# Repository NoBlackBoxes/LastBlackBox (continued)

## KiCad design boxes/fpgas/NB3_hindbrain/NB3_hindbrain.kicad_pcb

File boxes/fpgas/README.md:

# The Last Black Box : FPGAs
In this box, you will learn about fpgas...

## FPGAs
Field-programmable-gate-arrays-are-awesome.

<details><summary><i>Materials</i></summary><p>

Name|Depth|Description| # |Package|Data|Link|
:-------|:---:|:----------|:-----:|:-:|:--:|:--:|
NB3 Hindbrain|10|ICE40UP5K dev board with ADC/DAC|1|Circuit Boards|[-D-](/boxes/fpgas/NB3_hindbrain)|[-L-](VK)
Cable (MicroUSB-1m)|10|Micro-USB to Type-A cable (1 m)|1|Cables (001)|[-D-](/boxes/fpgas/)|[-L-](https://www.amazon.co.uk/gp/product/B07GBCKX49)

</p></details><hr>

### Hardware Description Languages
> Describing hardware layouts is very different than describing software algorithms. Hardware description languages allow you to describe precisely what pieces of transistor logic you want. They come in many flavours, but the most popular are **Verilog** and **VHDL**.

# Project

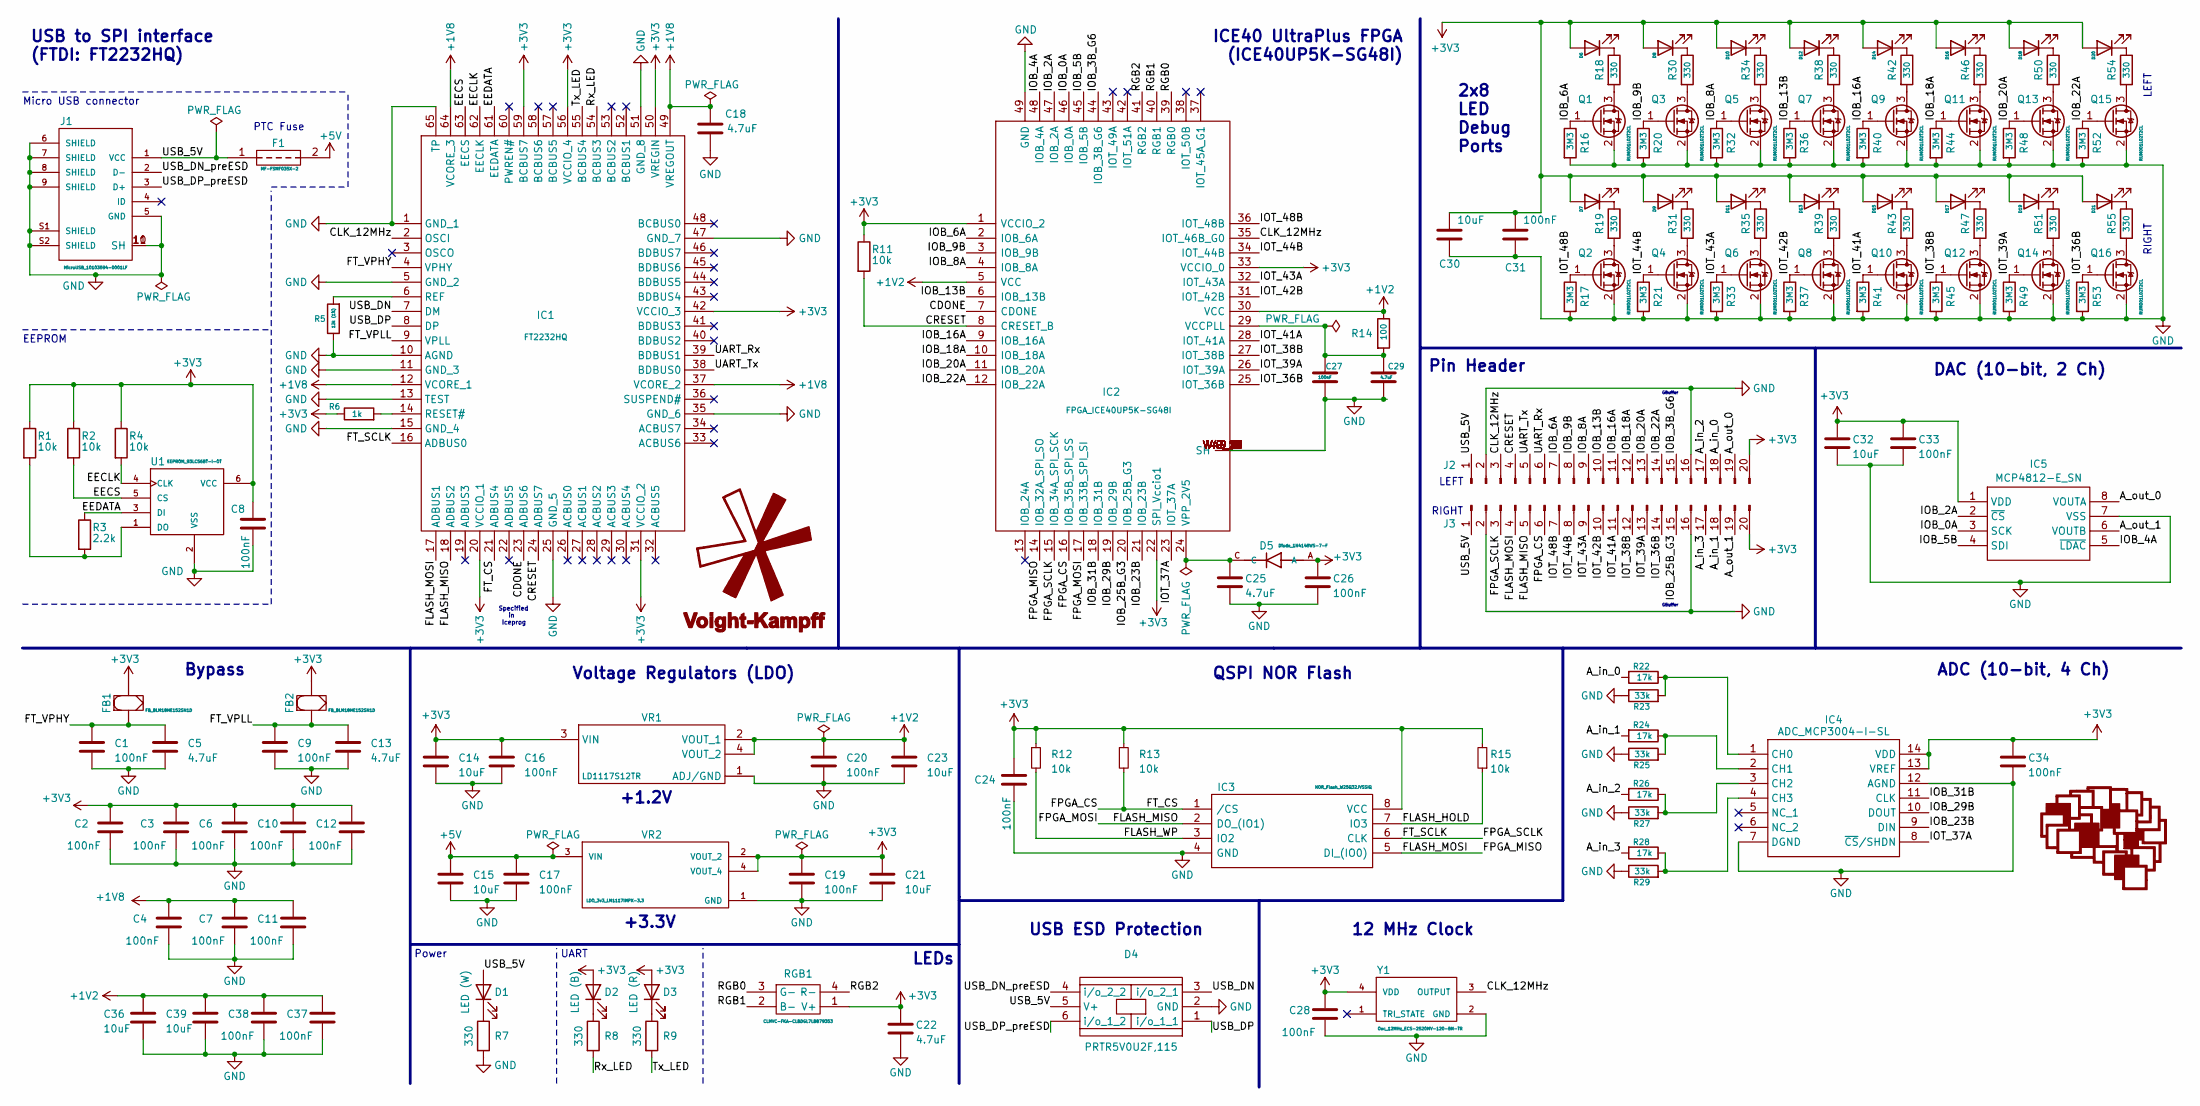
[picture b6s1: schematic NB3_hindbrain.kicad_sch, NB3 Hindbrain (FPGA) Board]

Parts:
C1, C2, C3, C4, C6, C7, C8, C9, C10, C11, C12, C16, C17, C19, C20, C24, C26, C27, C28, C31, C33, C34, C37, C38: 100nF; C_0402_1005Metric
C5, C13, C18, C22, C25, C29: 4.7uF; C_0603_1608Metric
C14, C15, C21, C23, C30, C32, C36, C39: 10uF; C_0603_1608Metric
D1: LED (W); LED_0402_1005Metric
D2, D6, D8, D10, D12, D14, D16, D18, D20: LED (B); LED_0402_1005Metric
D3, D7, D9, D11, D13, D15, D17, D19, D21: LED (R); LED_0402_1005Metric
D4: PRTR5V0U2F,115; ESD_Diodes_PRTR5V0U2F-115; Mouser Part Number 771-PRTR5V0U2F-T/R
D5: Diode_1N4148WS-7-F
F1: MF-FSMF035X-2; PTC_MF-FSMF035X-2; Mouser Part Number 652-MFFSMF035X-2
FB1, FB2: FB_BLM18HE152SN1D
G1: LOGO; Logo_NBB_5mm
G2: Logo_VK; Logo_VK_5mm
IC1: FT2232HQ; USBtoSerial_FT2232HQ; Mouser Part Number 895-FT2232HQ
IC2: FPGA_ICE40UP5K-SG48I; Manufacturer_Part_Number ICE40UP5K-SG48I; Mouser Part Number 842-ICE40UP5K-SG48I
IC3: NOR_Flash_W25Q32JVSSIQ; Manufacturer_Part_Number W25Q32JVSSIQ; Mouser Part Number 454-W25Q32JVSSIQ
IC4: ADC_MCP3004-I-SL; Mouser Part Number 579-MCP3004-I/SL
IC5: MCP4812-E_SN; DAC_MCP4812-E-SN; Mouser Part Number 579-MCP4812-E/SN
J1: MicroUSB_10103594-0001LF
J2, J3: Conn_01x20_Pin; PinHeader_1x20_P2.54mm_Vertical
Q1, Q2, Q3, Q4, Q5, Q6, Q7, Q8, Q9, Q10, Q11, Q12, Q13, Q14, Q15, Q16: RUM001L02T2CL; MOSFET_Nch_SOT-723_RUM001L02T2CL
R1, R2, R4, R11, R12, R13, R15: 10k; R_0402_1005Metric
R3: 2.2k; R_0402_1005Metric
R5: 12k (1%); R_0402_1005Metric
R6: 1k; R_0402_1005Metric
R7, R8, R9, R18, R19, R30, R31, R34, R35, R38, R39, R42, R43, R46, R47, R50, R51, R54, R55: 330; R_0402_1005Metric
R14: 100; R_0402_1005Metric
R16, R17, R20, R21, R32, R33, R36, R37, R40, R41, R44, R45, R48, R49, R52, R53: 3M3; R_0402_1005Metric
R22, R24, R26, R28: 17k; R_0402_1005Metric
R23, R25, R27, R29: 33k; R_0402_1005Metric
RGB1: CLMVC-FKA-CLBDGL7LBB79353; RGB_CLMVC-FKA-CLBDGL7LBB79353; Mouser Part Number 941-CLMVCFKACLBDGL7L
U1: EEPROM_93LC56BT-I-OT
VR1: LD1117S12TR; LDO_1v2_LD1117S12TR; Mouser Part Number 511-LD1117S12
VR2: LDO_3v3_LM1117IMPX-3.3; PARTREV O
Y1: Osc_12MHz_ECS-2520MV-120-BN-TR

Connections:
+1V2: C20.1, C23.1, C36.1, C37.2, C38.2, C39.1, IC2.5 (VCC), IC2.30 (VCC), R14.1, VR1.2 (VOUT_1), VR1.4 (VOUT_2)
+1V8: C4.2, C7.2, C11.2, C18.1, IC1.12 (VCORE_1), IC1.37 (VCORE_2), IC1.49 (VREGOUT), IC1.64 (VCORE_3)
+3V3: C2.2, C3.2, C6.2, C8.1, C10.2, C12.2, C14.1, C16.1, C19.1, C21.1, C22.1, C24.2, C26.1, C28.2, C30.1, C31.1, C32.1, C33.1, C34.1, D2.2 (A), D3.2 (A), D5.A, D6.2 (A), D7.2 (A), D8.2 (A), D9.2 (A), D10.2 (A), D11.2 (A), D12.2 (A), D13.2 (A), D14.2 (A), D15.2 (A), D16.2 (A), D17.2 (A), D18.2 (A), D19.2 (A), D20.2 (A), D21.2 (A), FB1.2, FB2.2, IC1.20 (VCCIO_1), IC1.31 (VCCIO_2), IC1.42 (VCCIO_3), IC1.50 (VREGIN), IC1.56 (VCCIO_4), IC1.59 (BCBUS7), IC2.1 (VCCIO_2), IC2.22 (SPI_Vccio1), IC2.33 (VCCIO_0), IC3.8 (VCC), IC4.13 (VREF), IC4.14 (VDD), IC5.1 (VDD), J2.20, J3.20, R1.1, R2.1, R4.1, R6.1, R11.1, R12.1, R13.1, R15.2, RGB1.1 (V+), U1.6 (VCC), VR1.3 (VIN), VR2.2 (VOUT_2), VR2.4 (VOUT_4), Y1.4 (VDD)
+5V: C15.1, C17.1, F1.2, VR2.3 (VIN)
/A_in_0: J2.18, R22.2
/A_in_1: J3.18, R24.2
/A_in_2: J2.17, R26.2
/A_in_3: J3.17, R28.2
/A_out_0: IC5.8 (VOUTA), J2.19
/A_out_1: IC5.6 (VOUTB), J3.19
/CDONE: IC1.23 (ADBUS6), IC2.7 (CDONE)
/CLK_12MHz: IC1.2 (OSCI), IC2.35 (IOT_46B_G0), J2.3, Y1.3 (OUTPUT)
/CRESET: IC1.24 (ADBUS7), IC2.8 (CRESET_B), J2.4, R11.2
/EECLK: IC1.62 (EECLK), R4.2, U1.4 (CLK)
/EECS: IC1.63 (EECS), R2.2, U1.5 (CS)
/EEDATA: IC1.61 (EEDATA), R3.1, U1.3 (DI)
/FLASH_HOLD: IC3.7 (IO3), R15.1
/FLASH_MISO: IC1.18 (ADBUS2), IC2.17 (IOB_33B_SPI_SI), IC3.2 (DO_(IO1)), J3.5
/FLASH_MOSI: IC1.17 (ADBUS1), IC2.14 (IOB_32A_SPI_SO), IC3.5 (DI_(IO0)), J3.4
/FLASH_WP: IC3.3 (IO2), R12.2
/FPGA_CS: IC1.21 (ADBUS4), IC2.16 (IOB_35B_SPI_SS), IC3.1 (/CS), J3.6, R13.2
/FPGA_SCLK: IC1.16 (ADBUS0), IC2.15 (IOB_34A_SPI_SCK), IC3.6 (CLK), J3.3
/FT_VPHY: C1.1, C5.1, FB1.1, IC1.4 (VPHY)
/FT_VPLL: C9.1, C13.1, FB2.1, IC1.9 (VPLL)
/IOB_0A: IC2.46 (IOB_0A), IC5.3 (SCK)
/IOB_2A: IC2.47 (IOB_2A), IC5.2 (~CS)
/IOB_3B_G6: IC2.44 (IOB_3B_G6), J2.15
/IOB_4A: IC2.48 (IOB_4A), IC5.5 (~LDAC)
/IOB_5B: IC2.45 (IOB_5B), IC5.4 (SDI)
/IOB_6A: IC2.2 (IOB_6A), J2.7, Q1.1 (G), R16.1
/IOB_8A: IC2.4 (IOB_8A), J2.9, Q5.1 (G), R32.1
/IOB_9B: IC2.3 (IOB_9B), J2.8, Q3.1 (G), R20.1
/IOB_13B: IC2.6 (IOB_13B), J2.10, Q7.1 (G), R36.1
/IOB_16A: IC2.9 (IOB_16A), J2.11, Q9.1 (G), R40.1
/IOB_18A: IC2.10 (IOB_18A), J2.12, Q11.1 (G), R44.1
/IOB_20A: IC2.11 (IOB_20A), J2.13, Q13.1 (G), R48.1
/IOB_22A: IC2.12 (IOB_22A), J2.14, Q15.1 (G), R52.1
/IOB_23B: IC2.21 (IOB_23B), IC4.9 (DIN)
/IOB_25B_G3: IC2.20 (IOB_25B_G3), J3.15
/IOB_29B: IC2.19 (IOB_29B), IC4.10 (DOUT)
/IOB_31B: IC2.18 (IOB_31B), IC4.11 (CLK)
/IOT_36B: IC2.25 (IOT_36B), J3.14, Q16.1 (G), R53.1
/IOT_37A: IC2.23 (IOT_37A), IC4.8 (~CS/SHDN)
/IOT_38B: IC2.27 (IOT_38B), J3.12, Q12.1 (G), R45.1
/IOT_39A: IC2.26 (IOT_39A), J3.13, Q14.1 (G), R49.1
/IOT_41A: IC2.28 (IOT_41A), J3.11, Q10.1 (G), R41.1
/IOT_42B: IC2.31 (IOT_42B), J3.10, Q8.1 (G), R37.1
/IOT_43A: IC2.32 (IOT_43A), J3.9, Q6.1 (G), R33.1
/IOT_44B: IC2.34 (IOT_44B), J3.8, Q4.1 (G), R21.1
/IOT_48B: IC2.36 (IOT_48B), J3.7, Q2.1 (G), R17.1
/RGB0: IC2.39 (RGB0), RGB1.3 (G-)
/RGB1: IC2.40 (RGB1), RGB1.2 (B-)
/RGB2: IC2.41 (RGB2), RGB1.4 (R-)
/Rx_LED: IC1.54 (BCBUS3), R8.2
/Tx_LED: IC1.55 (BCBUS4), R9.2
/UART_Rx: IC1.39 (BDBUS1), J2.6
/UART_Tx: IC1.38 (BDBUS0), J2.5
/USB_5V: D1.2 (A), D4.5 (V+), F1.1, J1.1 (VCC), J2.1, J3.1
/USB_DN: D4.3 (i/o_2_1), IC1.7 (DM)
/USB_DN_preESD: D4.4 (i/o_2_2), J1.2 (D-)
/USB_DP: D4.1 (i/o_1_1), IC1.8 (DP)
/USB_DP_preESD: D4.6 (i/o_1_2), J1.3 (D+)
GND: C1.2, C2.1, C3.1, C4.1, C5.2, C6.1, C7.1, C8.2, C9.2, C10.1, C11.1, C12.1, C13.2, C14.2, C15.2, C16.2, C17.2, C18.2, C19.2, C20.2, C21.2, C22.2, C23.2, C24.1, C25.2, C26.2, C27.2, C28.1, C29.2, C30.2, C31.2, C32.2, C33.2, C34.2, C36.2, C37.1, C38.1, C39.2, D4.2 (GND), IC1.1 (GND_1), IC1.5 (GND_2), IC1.10 (AGND), IC1.11 (GND_3), IC1.13 (TEST), IC1.15 (GND_4), IC1.25 (GND_5), IC1.35 (GND_6), IC1.47 (GND_7), IC1.51 (GND_8), IC1.65 (TP), IC2.49 (GND), IC2.V49_1 (SH), IC2.V49_2 (SH), IC2.V49_3 (SH), IC2.V49_4 (SH), IC2.V49_5 (SH), IC2.V49_6 (SH), IC2.V49_7 (SH), IC2.V49_8 (SH), IC2.V49_9 (SH), IC2.V49_10 (SH), IC2.V49_11 (SH), IC2.V49_12 (SH), IC2.V49_13 (SH), IC2.V49_14 (SH), IC2.V49_15 (SH), IC2.V49_16 (SH), IC2.V49_17 (SH), IC2.V49_18 (SH), IC2.V49_19 (SH), IC2.V49_20 (SH), IC2.V49_21 (SH), IC3.4 (GND), IC4.7 (DGND), IC4.12 (AGND), IC5.7 (VSS), J1.5 (GND), J1.6 (SHIELD), J1.7 (SHIELD), J1.8 (SHIELD), J1.9 (SHIELD), J1.10 (SH), J1.11 (SH), J1.S1 (SHIELD), J1.S2 (SHIELD), J2.2, J2.16, J3.2, J3.16, Q1.2 (S), Q2.2 (S), Q3.2 (S), Q4.2 (S), Q5.2 (S), Q6.2 (S), Q7.2 (S), Q8.2 (S), Q9.2 (S), Q10.2 (S), Q11.2 (S), Q12.2 (S), Q13.2 (S), Q14.2 (S), Q15.2 (S), Q16.2 (S), R5.1, R7.2, R16.2, R17.2, R20.2, R21.2, R23.1, R25.1, R27.1, R29.1, R32.2, R33.2, R36.2, R37.2, R40.2, R41.2, R44.2, R45.2, R48.2, R49.2, R52.2, R53.2, U1.2 (VSS), VR1.1 (ADJ/GND), VR2.1 (GND), Y1.2 (GND)
unnamed: D1.1 (K), R7.1
unnamed: D2.1 (K), R8.1
unnamed: D3.1 (K), R9.1
unnamed: D6.1 (K), R18.1
unnamed: D7.1 (K), R19.1
unnamed: D8.1 (K), R30.1
unnamed: D9.1 (K), R31.1
unnamed: D10.1 (K), R34.1
unnamed: D11.1 (K), R35.1
unnamed: D12.1 (K), R38.1
unnamed: D13.1 (K), R39.1
unnamed: D14.1 (K), R42.1
unnamed: D15.1 (K), R43.1
unnamed: D16.1 (K), R46.1
unnamed: D17.1 (K), R47.1
unnamed: D18.1 (K), R50.1
unnamed: D19.1 (K), R51.1
unnamed: D20.1 (K), R54.1
unnamed: D21.1 (K), R55.1
unnamed: IC1.6 (REF), R5.2
unnamed: IC1.14 (RESET#), R6.2
unnamed: C27.1, C29.1, IC2.29 (VCCPLL), R14.2
unnamed: C25.1, D5.C, IC2.24 (VPP_2V5)
unnamed: IC4.1 (CH0), R22.1, R23.2
unnamed: IC4.2 (CH1), R24.1, R25.2
unnamed: IC4.3 (CH2), R26.1, R27.2
unnamed: IC4.4 (CH3), R28.1, R29.2
unnamed: Q1.3 (D), R18.2
unnamed: Q2.3 (D), R19.2
unnamed: Q3.3 (D), R30.2
unnamed: Q4.3 (D), R31.2
unnamed: Q5.3 (D), R34.2
unnamed: Q6.3 (D), R35.2
unnamed: Q7.3 (D), R38.2
unnamed: Q8.3 (D), R39.2
unnamed: Q9.3 (D), R42.2
unnamed: Q10.3 (D), R43.2
unnamed: Q11.3 (D), R46.2
unnamed: Q12.3 (D), R47.2
unnamed: Q13.3 (D), R50.2
unnamed: Q14.3 (D), R51.2
unnamed: Q15.3 (D), R54.2
unnamed: Q16.3 (D), R55.2
unnamed: R1.2, R3.2, U1.1 (DO)

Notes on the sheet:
12 MHz Clock
LEFT
+1.2V
Power
ICE40 UltraPlus FPGA (ICE40UP5K-SG48I)
GBuffer
Pin Header
DAC (10-bit, 2 Ch)
PTC Fuse
UART
Specified in Iceprog
Micro USB connector
RIGHT
Voltage Regulators (LDO)
+3.3V
2x8 LED Debug Ports
LEDs
QSPI NOR Flash
Bypass
EEPROM
USB to SPI interface (FTDI: FT2232HQ)
USB ESD Protection
ADC (10-bit, 4 Ch)

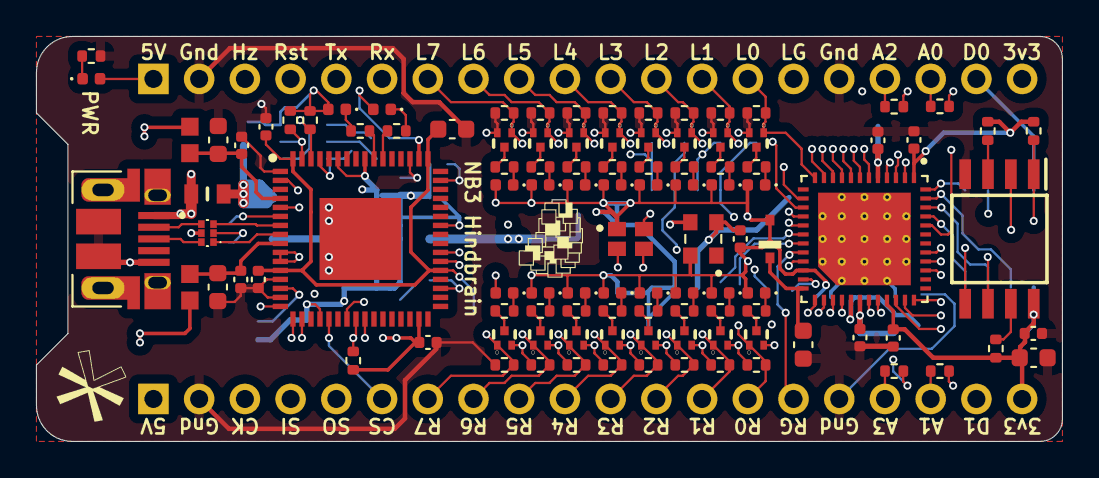
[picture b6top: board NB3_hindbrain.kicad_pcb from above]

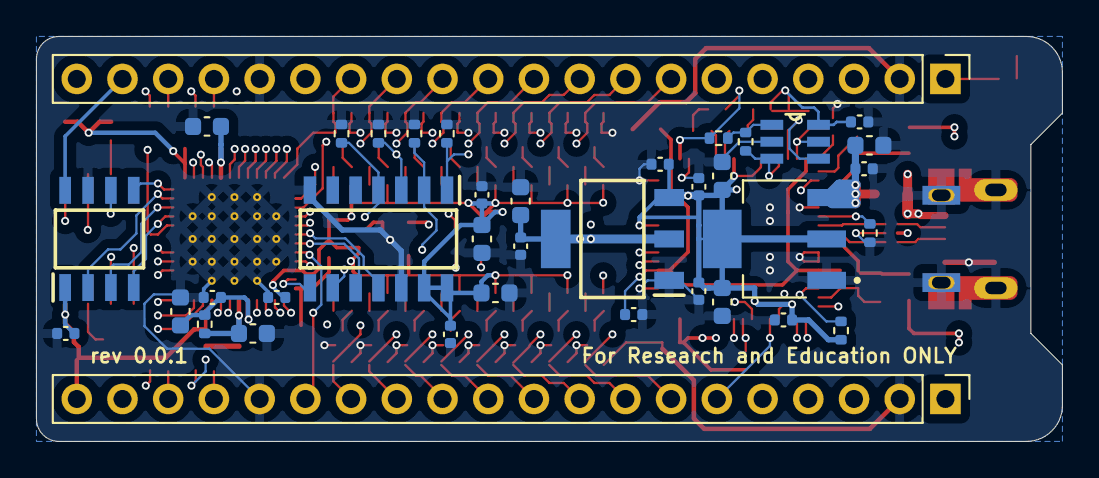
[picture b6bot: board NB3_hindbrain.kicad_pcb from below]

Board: 4 copper layers, 57.0 x 22.5 mm, 147 parts (38 on the bottom side), 107 nets.

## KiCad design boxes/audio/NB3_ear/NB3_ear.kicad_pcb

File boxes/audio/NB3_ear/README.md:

# Audio : NB3_ear

PCB design and fabrication for NB3 ear, a stereo i2s MEMS microphone

## Parts

- ICS-43434 from IvenSense: [datasheet](libraries/parts/Mic_ICS-43434/Mic_ICS-43434.pdf)

## Fabrication

### Generate files
0. Save front/back renders and 3D model (step)
1. Create "fab" folder in KiCAD project root
2. Export BOM (as CSV): File->Fabrication outputs->BOM
3. Edit BOM: Open as ODS and save as XLSX in "fab" folder
4. Generate Gerbers: File->Fabrication outputs->Gerbers [settings](NB3_ear_FAB_plot_settings.png)
5. Generate Drill: File->Fabrication outputs->Drill Files [settings](NB3_ear_FAB_drill_settings.png)
6. Generate Centroids: File->Fabrication outputs->Componenet Placement [settings](NB3_ear_FAB_pos_settings.png)
7. Zip entire fab folder (including BOM.xlsx)

### Upload boards(s) - PCBWay

#### Assembly Service
- Service: Turnkey Assembly
- Board type: Panelized PCBs
- Assembly: Top-Side
- Quantity: *160*

##### Other Parameters
- Number of unique Parts: 4
- Number of SMD Parts: 5
- Number of BGA/QFP Parts: 0
- Number of Through-Hole Parts: 0
			
#### PCB Specifications
- Board type: Panel by PCBWay
- Panel requirements: Panel in 2*4, total 20 sets=160pcs boards.
- Route Process: Panel as Tab Route
- X-out Allowance in Panel: Accept
- Different design in panel: 1
- Size: 56 x 78 mm
- Quantity: 20
- Layer: 2 Layers
- Material: FR-4: TG150-160
- Thickness: 1.6 mm
- Min track/spacing: 6/6mil
- Min hole size: 0.3mm
- Solder mask: White
- Silkscreen: Black
- Edge connector: No
- Surface finish: Immersion gold(ENIG) (1U"), "HASL" to "ENIG" No
- Via process: Tenting vias
- Finished copper: 1 oz Cu
- Remove product No.: No

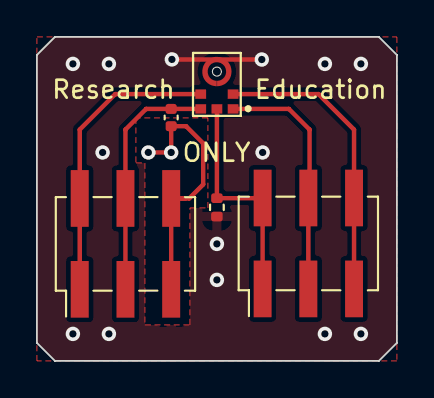
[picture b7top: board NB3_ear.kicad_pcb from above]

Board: 2 copper layers, 20.0 x 18.0 mm, 5 parts (0 on the bottom side), 6 nets.

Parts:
C1: 0.1 uF; C_0402_1005Metric
J1, J2: Conn_02x03_Odd_Even; PinHeader_2x03_P2.54mm_Vertical_SMD
MK1: Mic_ICS-43434
R1: 100k; R_0402_1005Metric

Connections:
+3.3V: C1.1, J1.3, J1.4, MK1.5 (VDD)
/LR: J2.5, J2.6, MK1.2 (LR)
/SCK: J1.1, J1.2, MK1.4 (SCK)
/SD: J2.1, J2.2, MK1.6 (SD), R1.2
/WS: J2.3, J2.4, MK1.1 (WS)
GND: C1.2, J1.5, J1.6, R1.1

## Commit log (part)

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2025-01-26 Update NB3 skull designs and hardware
2025-01-26 Added guide fpr BaB week 4
2025-01-28 Added "packaging" libs and scripts
2025-01-28 tweak
2025-01-28 Update arduino examples (analog)
2025-01-29 Update Arduino instructions for LAIC
2025-01-30 Draft work on adding price to BOM
2025-01-31 tweak materials
2025-01-31 Update all materials (again)
2025-02-01 Remove redundant boxes in BOM/Packing
2025-02-03 Update BaB session 5 teaching guide
2025-02-07 Update NB3 Charger (schematic) with power path
2025-02-08 Update NB3 Charger (schematic notes)
2025-02-10 Update NB3 Body (servo mounts for metal motors)
2025-02-11 Refactoring LBB Design library
2025-02-11 Refactor Design scripts and libs (still to do: animation)
2025-02-11 remove box parameters
2025-02-12 Work on python package print designs
2025-02-14 Update packaging design (layout text size)
2025-02-15 Update package designs (again)
2025-02-16 Work on NB3 Charger wiring
2025-02-17 Preliminary routing of NB3_charger
2025-02-18 Finish draft of NB3 Charger (submitted for Fab)
2025-02-18 Added overly complicated play_wav example...need an NB3 keyboard library
2025-02-20 Update NB3 Demos
2025-02-21 Work on NB3 demos (Listen draft)
2025-02-22 Update Mic code with mel features
2025-02-22 Added keyowrd model and labels
2025-02-22 Added build instructions for tflite 2.14 compatible libedgetpu
2025-02-23 Work on NB3 vision
2025-02-24 Working minimal Look demo
2025-02-26 Added task page for Remote NB3 (BaB7)
2025-02-28 Added wiring details for NB3_eyes
2025-03-03 Draft VS code SSH instruction doc
2025-03-04 Add "testing-audio" worksheet
2025-03-04 Update Linux+VS Code worksheet
2025-03-05 Tweak worksheets
2025-03-06 Added new Arduino CLI instructions
2025-03-06 Add distance sensor test code
2025-03-07 Refactoring libs (testing scripts)
2025-03-07 Draft parentage in LBB engine classes
2025-03-08 Simplify NB3 vision (but needs hardware encoder)
2025-03-08 Work on camera/stream overlay
2025-03-09 Draft NB3 Drone
2025-03-10 Work on draft NB3 Server
2025-03-10 Working on server performance (no frame polling)
2025-03-10 Update drone-NB3 draft to user Server
2025-03-11 Added webcam class (draft)
2025-03-11 Update drive (remove mydrive)
2025-03-13 Simplify server (command_handler)
2025-03-17 Ignore all "my*" files and folders (student projects)
2025-03-18 Update "Look" (2 faces)
2025-03-19 Update Drone project code and notes
2025-04-03 Add connect at home instructions
2025-04-04 Fix pyglet immutables
2025-04-28 Work on LiteRT examples
2025-05-02 Tweaks to LiteRT test ofr custom KWS model
2025-05-04 Removing mel processing from Mic class
2025-05-10 Add sshkeyboard to common libs
2025-05-11 Update KWS models
2025-05-12 Update folder structure for KWS
2025-05-12 Benchmark for KWS
2025-05-12 Work on quantized/scripted KWS model
2025-05-12 Back to stub Quant models
2025-05-12 Cleaner validation
2025-05-12 Working custom keyword RPi pytorch model
2025-05-13 Switch to normalised float inputs
2025-05-15 Fix remote NB3 links
2025-05-15 Work towards LBB site
2025-05-16 Add package install (netifaces)
2025-05-16 Update audio driver and testing instructions
2025-05-21 Add pretrained keyword model to repo
2025-06-02 Update NB3 Body PCB (rev 6)
2025-06-06 Tweak to RPi UART connect
2025-07-19 Test video preview GIFs
2025-07-19 Tweak (ctrl-click)
2025-07-19 Update README video thumbnails
2025-07-20 Update NB3 gif names
2025-07-20 Remove "site" folder
2025-07-21 Update BOM/Packing lists
2025-07-21 Add inventory to materials.csv and BOM
2025-07-22 Update inventory (and enforce UTF-8)
2025-07-28 Update NB3 Mouth PCB Fab
2025-07-29 Update inventory and generate bootcamp packing list
2025-08-03 Report speaker WAV inconsistencies
2025-08-15 Update inventory
2025-08-15 Update package names and include in "materials included"
2025-09-01 Add motor anatomy
2025-09-02 Update python remote server NB3 demo
2025-09-02 Create objectDetection.py
    Added pre-trained neural network for object detection
2025-09-04 Added sound info test
2025-09-05 Add face detector to vision box
2025-09-19 Add portrait LBB layout
2025-09-23 Update chatNB3 2025
2025-09-24 Update README for chatNB3
2025-10-09 Update bootcamp video and lesson planning
2025-10-14 Update video scripts
2025-10-15 Work on socket data examples
2025-10-15 Add socket client (and some crude plotting)
2025-10-15 Update socket_server
2025-10-15 Work on fast plotting (and audio tweaks)
2025-10-24 Added "shell" README with example .bashrc
2025-10-25 Fixed NB£ plots and demos of plotting
2025-10-25 Update image processing examples with "webcam" option
2025-10-26 Simpligy NB3 camera capture API
2025-10-26 Work on interactive slider for image processing demos
2025-10-29 Cleaning up HTML, CSS, and JS demos
2025-10-30 Remove course curricula correspondence
2025-10-30 refactor electrons
2025-10-30 refactor light
2025-10-30 refactor motors
2025-10-30 refactor transistor box
2025-10-30 refactor circuits
2025-10-30 refactor logic
2025-10-30 refactor memory
2025-10-31 refactor computers
2025-10-31 refactor control
2025-10-31 refactor power
2025-10-31 refactor systems
2025-10-31 refactor python
2025-10-31 refactor websites
2025-10-31 refactor security
2025-10-31 refactor audio
2025-10-31 refactor learning
2025-11-01 refactor out concept of "depth" in course lessons/tasks/boxes
2025-11-01 Update BOM generators (needs testing and comparison)
2025-11-01 Remove part models
2025-11-01 Added Linux "alias" instructions to courses
2025-11-01 Tweaks to image processing NB3 examples (and tests)
2025-11-01 Remove print in pyglet client socket
2025-11-01 Slight tweak to socket serial server (adjustable sample number)
2025-11-03 Draft signal processing tasks
2025-11-04 Update heartbeat stream
2025-11-04 Update socket clients
2025-11-04 Tweaks to Pyglet plotting
2025-11-04 Added live pyglet plot (draft) for FFT
2025-11-06 Update HTML
2025-11-06 Added socket video and updated course READMEs
2025-11-06 Remove unused lib from freq stream
2025-11-06 Work on server examples
2025-11-06 Update course READMEs
2025-11-07 Javascript example tweak
2025-11-08 Work on signal processing examples
2025-11-08 Draft work on audio timing detector (noisy!)
2025-11-09 Reorganize signal processing examples (timing hard), and add volume meter to utils
2025-11-10 Update server lesson text
2025-11-10 Seperate simple/simplest socket http servers
2025-11-11 Added HTTP lesson content/notes
2025-11-11 Tweak to NB3 server test example
2025-11-11 Tweak to style sheet comment
2025-11-12 Update server videos and lessons
2025-11-13 Add spectrogram example to audio signal processing
2025-11-14 Update typo in bootcamp main README
2025-11-14 Switch "build a brain" from bash_aliases to bashrc (for consistency)
2025-11-15 Bump js-yaml from 4.1.0 to 4.1.1 in /boxes/servers/node/vscode/canvas
    Bumps [js-yaml](https://github.com/nodeca/js-yaml) from 4.1.0 to 4.1.1.
    - [Changelog](https://github.com/nodeca/js-yaml/blob/master/CHANGELOG.md)
    - [Commits](https://github.com/nodeca/js-yaml/compare/4.1.0...4.1.1)
    ---
    updated-dependencies:
    - dependency-name: js-yaml
2025-11-15 Bump js-yaml in /boxes/servers/node/vscode/explainer-recorder
    Bumps [js-yaml](https://github.com/nodeca/js-yaml) from 4.1.0 to 4.1.1.
    - [Changelog](https://github.com/nodeca/js-yaml/blob/master/CHANGELOG.md)
    - [Commits](https://github.com/nodeca/js-yaml/compare/4.1.0...4.1.1)
    ---
    updated-dependencies:
    - dependency-name: js-yaml
2025-11-15 Work on song generation and visualization
2025-11-17 Added pyshrink command to BaB readme
2025-11-17 Bump js-yaml in /boxes/servers/node/vscode/code-explainer
    Bumps [js-yaml](https://github.com/nodeca/js-yaml) from 4.1.0 to 4.1.1.
    - [Changelog](https://github.com/nodeca/js-yaml/blob/master/CHANGELOG.md)
    - [Commits](https://github.com/nodeca/js-yaml/compare/4.1.0...4.1.1)
    ---
    updated-dependencies:
    - dependency-name: js-yaml
2025-11-19 Switching to pathlib to get "Home" folder in a more cross platform way
2025-11-19 Cleanup signal-gen/proc examples in prep for video
2025-11-20 Update signal processing demos (Config.repo_path)
2025-11-20 Update image processing examples with auto camera lib selection (NB3 vs Webcam)
2025-11-20 Refactoring old getlogin as well simpler Serial setup/open (needs testing)
2025-11-20 Switch to NB3 audio default ("MAX") device naming
2025-11-20 Fix horn sound
2025-11-21 Testing coral demos
2025-11-22 Switch to soundfile for more complex WAV
2025-11-24 Update for Signal Processing video (new GiI speed test)
2025-11-24 Slower GIFs (less distracting on GitHub Site)
2025-11-24 Cleaning stale content
2025-11-24 Cleaning prior to engine refactor
2025-11-24 Update to simpler "course model"
2025-11-25 Remove NB3 Sound Streaming to browser
2025-11-27 Refactor supervised learning walkthrough examples
2025-11-27 Tweaks to MLP in supervised learning example
2025-11-27 Tweak weight init supervised demo
2025-11-28 Update Light,Cameras,Noise lesson (video)
2025-11-28 Update libcamera commands to rpicam
2025-11-29 Update streaming images video
2025-11-29 Tweaks to opencv FaceDNN
2025-11-29 Added draft OpenAI based GPT-in-NB3
2025-12-02 Refactor image processing (online vs offline)
2025-12-02 Work on offline image processing examples
2025-12-05 Add HSV space image
2025-12-20 Restructured repo for easier install using uv
2026-02-13 changes to ai workshop structure
2026-02-13 add environment description and yml
2026-02-13 remove env files
2026-02-13 add environment setup link to README files
2026-02-16 add elevenlabs api test script
2026-02-23 update python env link
2026-03-04 add inline explanatory comments
2026-03-12 Add notebooks and setup for hackathon vision course
2026-03-13 remove api test script from version control
2026-03-13 Add NB3 demo and refactor audio workshop scripts for shared config and clearer docs
2026-03-13 audio workshop: WAV pipeline + Pi GPIO playback, 02 save-only
    - Output WAV from 00 and 02 (MP3 only as intermediate, then removed)
    - 01 reads my_00_question.wav; pipeline stays save-only, no auto-play in 02
    - Add utils/nb3_audio.py for MP3→WAV and NB3 aplay (plughw:3)
    - demo: play intro/reply on laptop (ffplay) and Pi (play_mp3_on_nb3), no kept files
    - README: document WAV outputs and add aplay command for playing WAV on Pi
2026-03-13 audio workshop: student-facing README, docstrings, aplay fix
    README:
    - Drop venv step; assume env already active, add git pull + install + .env
    - Document ffmpeg as required for MP3→WAV; table for ffmpeg/ffplay/aplay/arecord
    - Add copy-paste cd commands from repo root for pip, touch .env, pipeline, demo, aplay
    - Renumber setup (1.1–1.3), add “What’s in this folder” and “Playing the WAV”
    - Shorten workshop ideas and notes
2026-03-13 clean up terminal output
2026-03-13 add hackathon ideas
2026-03-13 audio workshop: STT language_code=en, tag_audio_events=False to avoid locale tags in transcript
2026-03-19 Added a few group photos to test out the face tracking
2026-03-19 Prepare vision demo notebooks for Chromebook-only setup
2026-03-20 ignore model weights
2026-03-20 Delete course/versions/ai-workshops/02_vision/_resources/chromebook/videos/recorded_video.mp4
    delete recorded video
2026-03-20 Vision workshop updates
    - Use recorded images/videos instead of webcam
    - Update notebooks (01, 02, 03)
    - Update setup instructions
    - Update assets (filters)
2026-03-20 Added python script for running face tracking and landmark detection on raspberry pi
2026-03-21 Updated ai vision notebooks
2026-03-21 Update Chromebook vision workshop setup
2026-04-13 Added command for SSh connection
2026-04-15 added Activate to project readme files
2026-05-15 Update vimeo link to Current video
2026-05-15 update teaching guide for enb course, session 01
2026-05-22 Update `Current.md`: propogate to all courses
2026-05-28 Add gitignore entries for site build output
    - course/versions/*/.docfx-staging/ transient docfx staging
    - /docs/ built site (regenerated by build_all.py)
2026-05-28 Add docfx site build tooling
    course/tools/build_all.py drives the build; course/tools/docfx/ holds
    build_site.py, rewrite_links.py, and a shared template (docfx.json,
    toc.yml, CSS/JS) with per-course overrides.
2026-05-28 Add Crick course content
    Five-day variant for the Francis Crick Institute bootcamp: session
    templates + READMEs, landing/sessions overrides, secondary logo,
    and the course poster.
2026-05-28 Set PYTHONPATH=libs in build_all subprocesses
2026-05-29 Bump GHA actions to Node 24 versions
2026-06-09 Remove Crick logo from landing page
2026-06-09 Add Bootcamp course site
2026-06-10 Add Build a Brain course site
